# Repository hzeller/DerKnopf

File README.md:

Remote controlled volume knob
=============================

_**Knopf, der** German: button, knob (Pronounciation: /knɔpf/)_

A project to upgrade an amplifier volume knob from a simple regular
potentiometer to a digital one that still can be controlled
directly at the amplifier but also via an infrared remote control.

Replaces the regular potentiometer with a [DS1882] and a rotational encoder.
Visual feedback with a charlie-plexed LED ring.

The interesting part is the infrared remote control: another rotational encoder,
with an infrared transmitter: a wireless extension of the volume knob.

The rotational encoders have a secondary push-button function which is used to
enable muting. Another press on that button will un-mute and go back to the
original volume.

# Remote control sender
The [sender](./pcb/remote-control) is a 20mm round PCB and thus roughly the
size of the volume knob and the diameter of a CR2032 battery.

Provides a rotational encoder with an integrated button (used for 'mute'), two
Infrared LEDs to send.
Microcontroller: Attiny44. Quiescent current: < 0.2 μA. Runs on CR2032.

Top                    | Side                       | Bottom
-----------------------|----------------------------|--------------------------
||

TODO: build acryilic housing.

Code in [sender/](./sender) directory.

# DigiPot Receiver

The [receiver](pcb/digi-pot) behaves like a logarithmic stereo potentiomter.
It takes an input signal from a local rotational encoder or the infrared
signal (amplified and prepared with a Vishay TSOP75338).
It provides two 'potentiometer' outputs. The local encoder has a 32 step/turn
resolution of which 30 are used (to have a visual 'gap' between min and max
like in a regular pot).

Microcontroller: Attiny48.
Runs on +5V (digital processing) and +/-6V (Analog). For these voltge rails,
there is a little separate [power supply PCB](./pcb/power)

Code in [receiver/](./receiver) directory.

Render                      |  Bottom                      | Shallow side view
----------------------------|------------------------------|----------------------------|
| (This early revision required some bodge resistors)||

# LED Ring
The [LED ring](./pcb/led-ring) is mounted on the front-panel of the amplifier
around the volume knob. In this case, this is a 19mm knob, so the ring is 20mm.

It contains 30 charlie-plexed LEDs to display the current 'position' and the
TSOP IR module. On mute, the current volume position is blinking (controlled by
the [DigiPot](./pcb/digi-pot)).

The round board connects with the main receiver board via a 12 connect,
0.5mm pitch flat flex cable.

Render                       | Real
-----------------------------|----------------------
 | 

### Mounted on Amplifier and final Remote Control

[DS1882]: https://datasheets.maximintegrated.com/en/ds/DS1882.pdf

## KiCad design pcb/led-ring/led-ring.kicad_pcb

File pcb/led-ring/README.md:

Led-Ring
========

Led-ring with 30 charlie-plexed LEDs to display the position of the pot.
Also, since this is mounted on the front-panel, the place for the IR receiver.

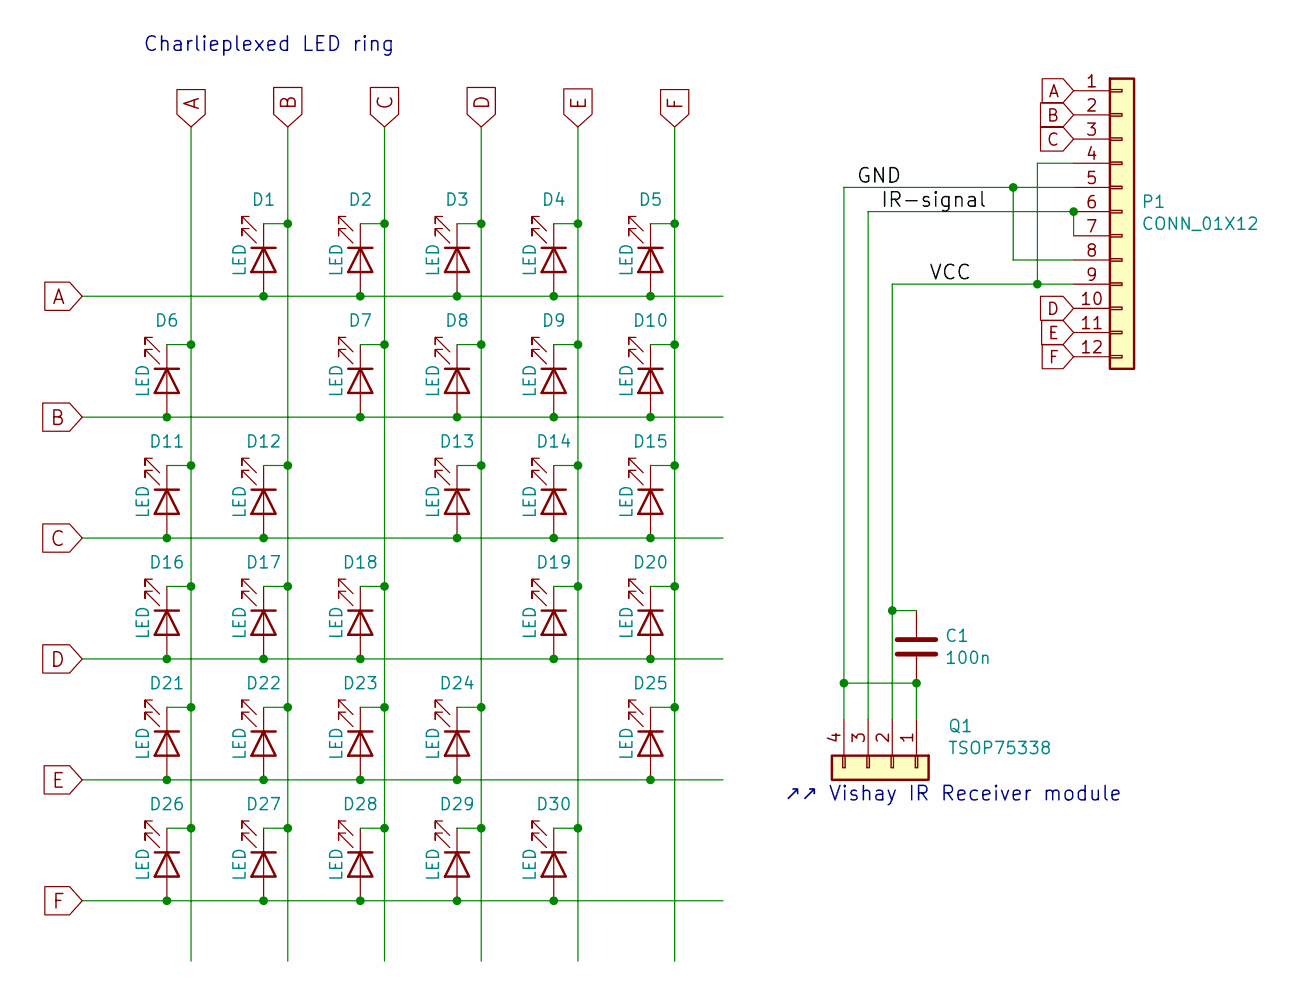
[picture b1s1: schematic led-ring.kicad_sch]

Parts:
C1: 100n; C_0603_1608Metric
D1, D2, D3, D4, D5, D6, D7, D8, D9, D10, D11, D12, D13, D14, D15, D16, D17, D18, D19, D20, D21, D22, D23, D24, D25, D26, D27, D28, D29, D30: LED; LED_0603_1608Metric
P1: CONN_01X12; FlatFlex
Q1: TSOP75338; TSOP75xx

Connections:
/GND: C1.2, P1.5, P1.8, Q1.1, Q1.4
/IR-signal: P1.6, P1.7, Q1.3
/VCC: C1.1, P1.4, P1.9, Q1.2
A: D1.2 (A), D2.2 (A), D3.2 (A), D4.2 (A), D5.2 (A), D6.1 (K), D11.1 (K), D16.1 (K), D21.1 (K), D26.1 (K), P1.1
B: D1.1 (K), D6.2 (A), D7.2 (A), D8.2 (A), D9.2 (A), D10.2 (A), D12.1 (K), D17.1 (K), D22.1 (K), D27.1 (K), P1.2
C: D2.1 (K), D7.1 (K), D11.2 (A), D12.2 (A), D13.2 (A), D14.2 (A), D15.2 (A), D18.1 (K), D23.1 (K), D28.1 (K), P1.3
D: D3.1 (K), D8.1 (K), D13.1 (K), D16.2 (A), D17.2 (A), D18.2 (A), D19.2 (A), D20.2 (A), D24.1 (K), D29.1 (K), P1.10
E: D4.1 (K), D9.1 (K), D14.1 (K), D19.1 (K), D21.2 (A), D22.2 (A), D23.2 (A), D24.2 (A), D25.2 (A), D30.1 (K), P1.11
F: D5.1 (K), D10.1 (K), D15.1 (K), D20.1 (K), D25.1 (K), D26.2 (A), D27.2 (A), D28.2 (A), D29.2 (A), D30.2 (A), P1.12

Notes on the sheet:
↗↗ Vishay IR Receiver module
Charlieplexed LED ring

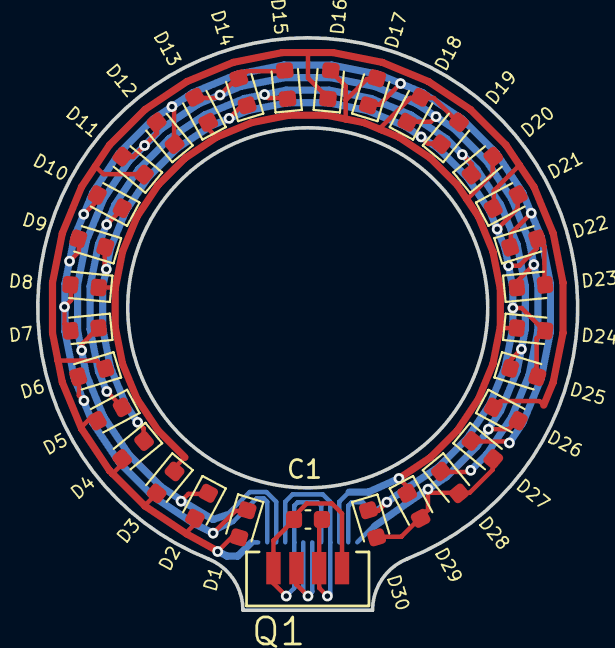
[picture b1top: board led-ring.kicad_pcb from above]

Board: 2 copper layers, 30.0 x 31.8 mm, 33 parts (1 on the bottom side), 9 nets.

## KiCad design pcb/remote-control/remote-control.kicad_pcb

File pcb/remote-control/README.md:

Remote Control
==============

The remote control, operated with an Attiny44 on a CR2032 battery. Processor
gets woken up from power down state on state change of the inputs, so quiescent
current is less than 0.2 μA.

It is not clear yet if the CR2032 increase in internal resistance over time will
be sufficient for our desired peak-current of 120mA through the IR LEDs (only
partially on, so average current ~40mA). So future revisions might consider
adding some electrolytic capacitors (but we'd need > 4700uF to power one
transmit of about 64ms * 40mA * 3V ~= 8mJ), or changing the battery (CR2450 or
even two AAA or AAAA).

With optional 1M pullups for the mechanical encoder, as these sometimes get
stuck in some half position, draining current through the pull-ups. The
standard pullups inside the attiny are aorund 60k (Note: this feature is not
used in the assembly below, just using the internal resistors.)

The programming header shown in the schematic does not have a component
associated on the board as it was too bulky.

Single-sided board for simple home-etching.

## BOM
  * 1x rotational encoder with push-button (here: EN11-HSB1AQ20, but might consider EN11-HSM1AF15 in the future for better mounting. See [EN11-datasheet])
  * 1x Attiny44
  * 1x 22μF ceramic capacitor (1206)
  * 1x 100n ceramic capacitor (0603)
  * 2x 1M resistor (0603)
  * 1x 4.7Ohm resistor (0805)
  * 1x MTM232270 N-channel Mosfet (SOT-323)

Top                    | Side                       | Bottom
-----------------------|----------------------------|--------------------------
||

[EN11-datasheet]: http://www.bitechnologies.com/pdfs/en11.pdf

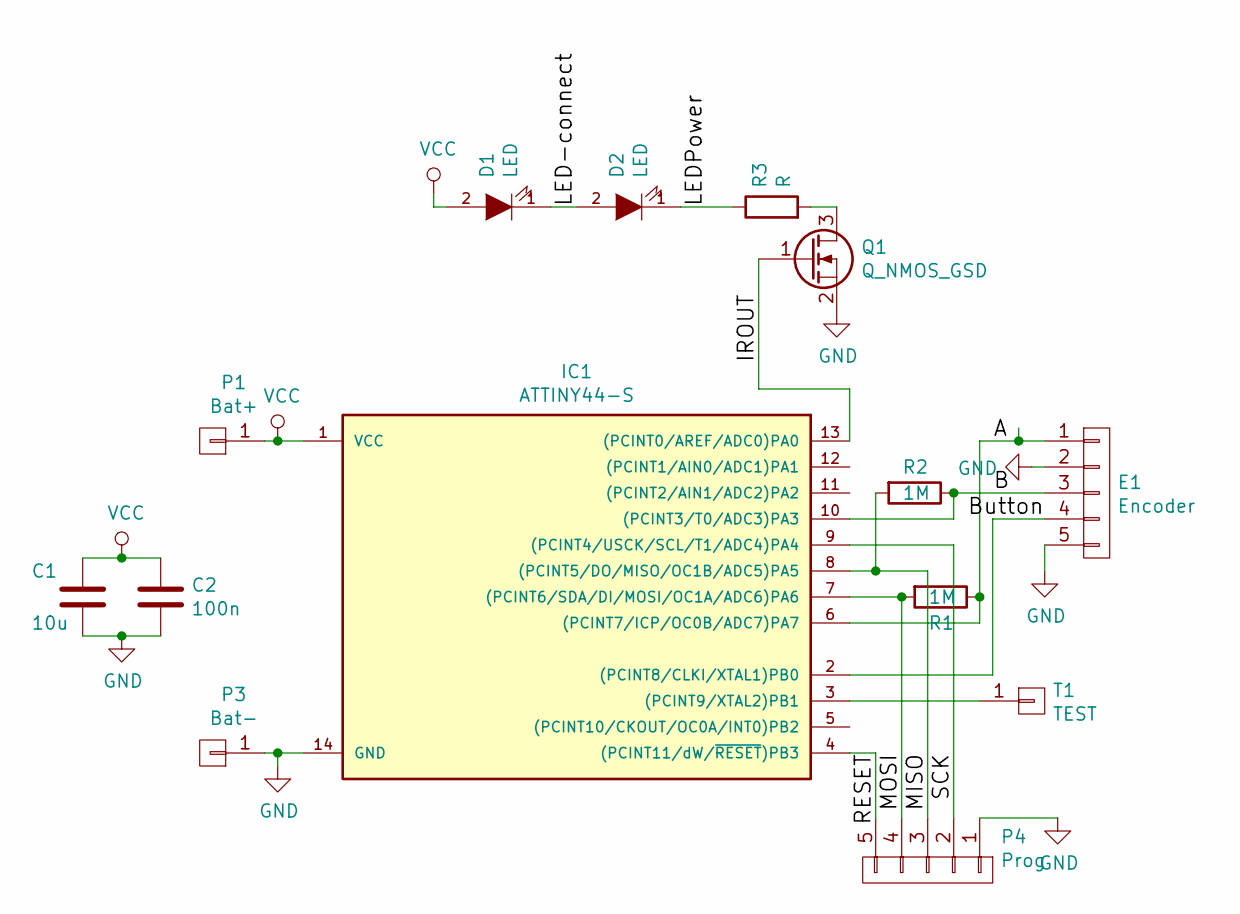
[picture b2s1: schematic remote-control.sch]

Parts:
C1: 10u; C_0805
C2: 100n
D1, D2: LED; LED-5MM
E1: Encoder; MechanicalEncoder
IC1: ATTINY44-S; SOIC-14_N
P1: Bat+; Pin_Header_Straight_1x01
P3: Bat-; Pin_Header_Straight_1x01
P4: Prog
Q1: Q_NMOS_GSD; SOT-323
R1, R2: 1M; R_0603
R3: R; R_0805
T1: TEST; TestPoint

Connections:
/A: E1.1, IC1.6 ((PCINT7/ICP/OC0B/ADC7)PA7), R1.1
/B: E1.3, IC1.10 ((PCINT3/T0/ADC3)PA3), R2.1
/Button: E1.4, IC1.2 ((PCINT8/CLKI/XTAL1)PB0)
/IROUT: IC1.13 ((PCINT0/AREF/ADC0)PA0), Q1.1 (G)
/LED-connect: D1.1 (K), D2.2 (A)
/LEDPower: D2.1 (K), R3.1
/MISO: IC1.8 ((PCINT5/DO/MISO/OC1B/ADC5)PA5), P4.3, R2.2
/MOSI: IC1.7 ((PCINT6/SDA/DI/MOSI/OC1A/ADC6)PA6), P4.4, R1.2
/RESET: IC1.4 ((PCINT11/dW/~RESET~)PB3), P4.5
/SCK: IC1.9 ((PCINT4/USCK/SCL/T1/ADC4)PA4), P4.2
GND: C1.2, C2.2, E1.2, E1.5, IC1.14 (GND), P3.1, P4.1, Q1.2 (S)
unnamed: IC1.3 ((PCINT9/XTAL2)PB1), T1.1
unnamed: Q1.3 (D), R3.2
VCC: C1.1, C2.1, D1.2 (A), IC1.1 (VCC), P1.1

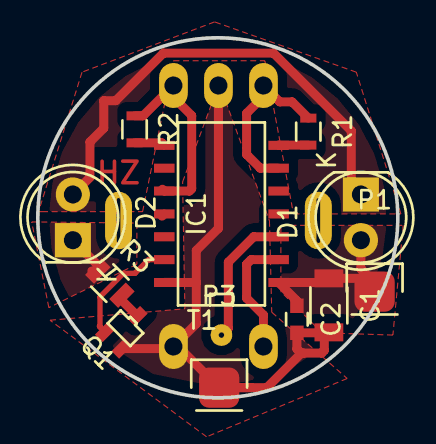
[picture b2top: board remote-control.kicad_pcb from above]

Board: 2 copper layers, 20.0 x 20.0 mm, 13 parts (1 on the bottom side), 12 nets.

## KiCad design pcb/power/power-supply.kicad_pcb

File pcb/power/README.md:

Power supply
============

The DigiPot needs 5V for digital operation and +/- 6V for the analog part.
Assuming that we already have some symmetric power in the amplifier, this
creates the necessary voltages. The current demands on the analog rails are
miniscule, so small SOT89-3 are sufficient for the task.

The 5V rail needs something in the 30mA range (operate microcontroller,
LEDs on LED ring and optical encoder), so depending on the input
voltage that could be some noticeable generated heat, hence we use a TO220 case.

Single sided board for simple home-etching.

## BOM

 * 1x 78L06 SOT89-3
 * 1x 79L06 SOT89-3
 * 1x 7805 TO220
 * 3x 100n capacitor, 0805
 * 2x 10uF ceramic capacitor, 50V, 1206

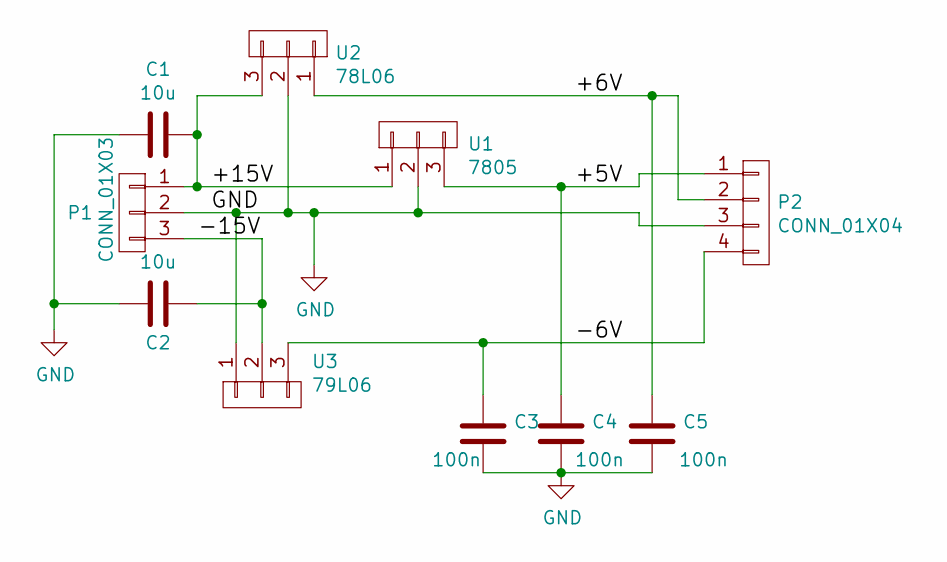
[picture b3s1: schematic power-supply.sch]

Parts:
C1, C2: 10u; C_1206_HandSoldering
C3, C4, C5: 100n; C_0805_HandSoldering
P1: CONN_01X03; Pin_Header_Straight_1x03
P2: CONN_01X04; Pin_Header_Straight_1x04
U1: 7805; TO-220_Neutral123_Horizontal_LargePads
U2: 78L06; SOT89-3_Housing_Handsoldering
U3: 79L06; SOT89-3_Housing_Handsoldering

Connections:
/+5V: C4.1, P2.1, U1.3
/+6V: C5.1, P2.2, U2.1
/+15V: C1.1, P1.1, U1.1, U2.3
/-6V: C3.1, P2.4, U3.3
/-15V: C2.1, P1.3, U3.2
GND: C1.2, C2.2, C3.2, C4.2, C5.2, P1.2, P2.3, U1.2, U2.2, U3.1

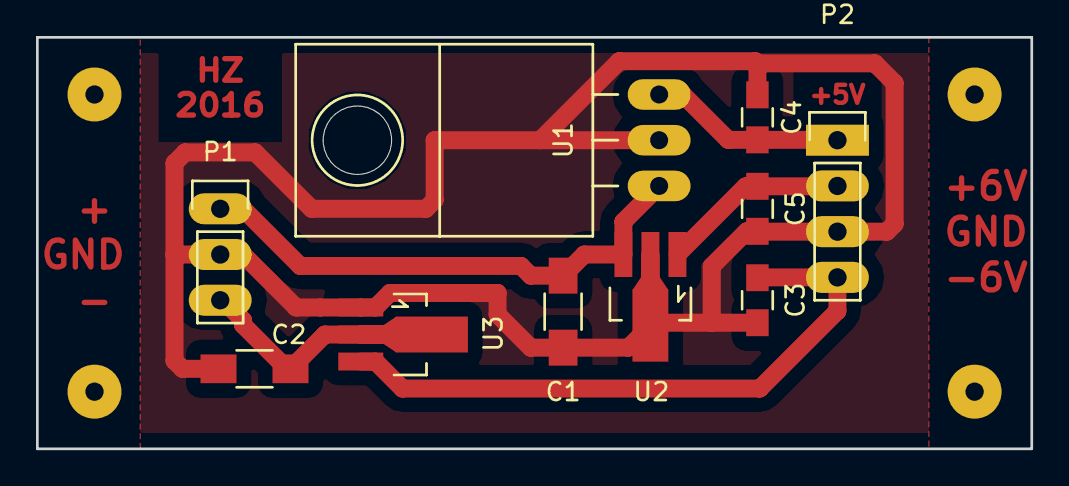
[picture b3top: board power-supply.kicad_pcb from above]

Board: 2 copper layers, 55.2 x 22.9 mm, 14 parts (0 on the bottom side), 6 nets.

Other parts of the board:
R: D; Pin_Header_Straight_1x01
R#2, R#3, R#4: D; Pin_Header_Straight_1x01

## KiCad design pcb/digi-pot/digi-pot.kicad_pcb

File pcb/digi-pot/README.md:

DigiPot
=======

The actual simulated pot with connectors for the LED ring, the IR receiver and
a local optical rotational encoder to have the feel of a local potentiometer.

This encoder replaces an existing high-quality ALPS potentiometer with 30 detents.
It is surprisingly hard to find a mechanical encoder with the same solid feel
and 32 detents (most mechanical enoders only go to 20 steps/turn).

The CUI optical encoder is perfect for this job but about as expensive as the
potentiometer it replaces.

## BOM

 * 2x 4.7k 0603 resistor
 * 4x 100n 0603 capacitor
 * 2x (4x75 Ohm) resistor network.
 * 1x Attiny48
 * 1x DS1882
 * 1x CUI C14D32P-A3 optical encoder.
 * 1x FlatFlex 12Pin connector.

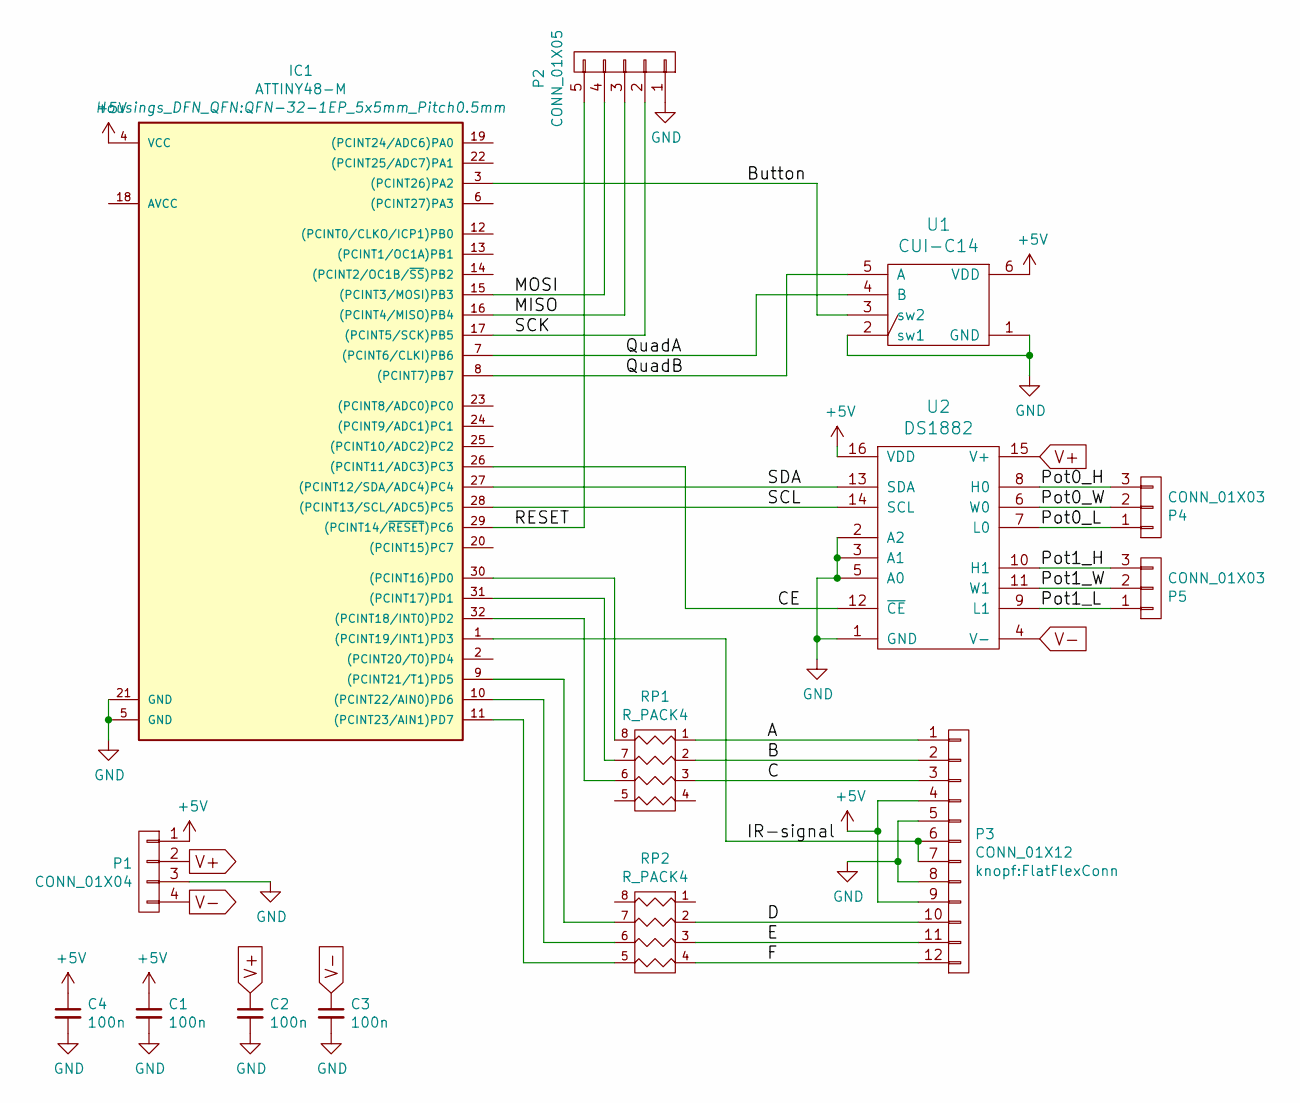
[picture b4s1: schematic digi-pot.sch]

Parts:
C1, C2, C3, C4: 100n; C_0805
IC1: ATTINY48-M; QFN-32-1EP_5x5mm_Pitch0.5mm
P1: CONN_01X04; Pin_Header_Straight_1x04
P2: CONN_01X05; Pin_Header_Straight_1x05
P3: CONN_01X12; FlatFlexConn
P4, P5: CONN_01X03; Pin_Header_Straight_1x03
RP1, RP2: R_PACK4; R_Array_Convex_4x0603
U1: CUI-C14
U2: DS1882; TSSOP-16_4.4x5mm_Pitch0.65mm

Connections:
+5V: C1.1, C4.1, IC1.4 (VCC), P1.1, P3.4, P3.9, U1.6 (VDD), U2.16 (VDD); also elsewhere on the board
/A: P3.1, RP1.1
/B: P3.2, RP1.2
/Button: IC1.3 ((PCINT26)PA2), U1.3 (sw2)
/C: P3.3, RP1.3
/CE: IC1.26 ((PCINT11/ADC3)PC3), U2.12 (~CE)
/D: P3.10, RP2.2
/E: P3.11, RP2.3
/F: P3.12, RP2.4
/IR-signal: IC1.1 ((PCINT19/INT1)PD3), P3.6, P3.7
/MISO: IC1.16 ((PCINT4/MISO)PB4), P2.3
/MOSI: IC1.15 ((PCINT3/MOSI)PB3), P2.4
/Pot0_H: P4.3, U2.8 (H0)
/Pot0_L: P4.1, U2.7 (L0)
/Pot0_W: P4.2, U2.6 (W0)
/Pot1_H: P5.3, U2.10 (H1)
/Pot1_L: P5.1, U2.9 (L1)
/Pot1_W: P5.2, U2.11 (W1)
/QuadA: IC1.7 ((PCINT6/CLKI)PB6), U1.4 (B)
/QuadB: IC1.8 ((PCINT7)PB7), U1.5 (A)
/RESET: IC1.29 ((PCINT14/~RESET~)PC6), P2.5
/SCK: IC1.17 ((PCINT5/SCK)PB5), P2.2
/SCL: IC1.28 ((PCINT13/SCL/ADC5)PC5), U2.14 (SCL); also elsewhere on the board
/SDA: IC1.27 ((PCINT12/SDA/ADC4)PC4), U2.13 (SDA); also elsewhere on the board
GND: C1.2, C2.2, C3.2, C4.2, IC1.5 (GND), IC1.21 (GND), P1.3, P2.1, P3.5, P3.8, U1.1 (GND), U1.2 (sw1), U2.1 (GND), U2.2 (A2), U2.3 (A1), U2.5 (A0)
unnamed: IC1.9 ((PCINT21/T1)PD5), RP2.7 (R2)
unnamed: IC1.10 ((PCINT22/AIN0)PD6), RP2.6 (R3)
unnamed: IC1.11 ((PCINT23/AIN1)PD7), RP2.5 (R4)
unnamed: IC1.30 ((PCINT16)PD0), RP1.8 (R1)
unnamed: IC1.31 ((PCINT17)PD1), RP1.7 (R2)
unnamed: IC1.32 ((PCINT18/INT0)PD2), RP1.6 (R3)
V+: C2.1, P1.2, U2.15 (V+)
V-: C3.1, P1.4, U2.4 (V-)

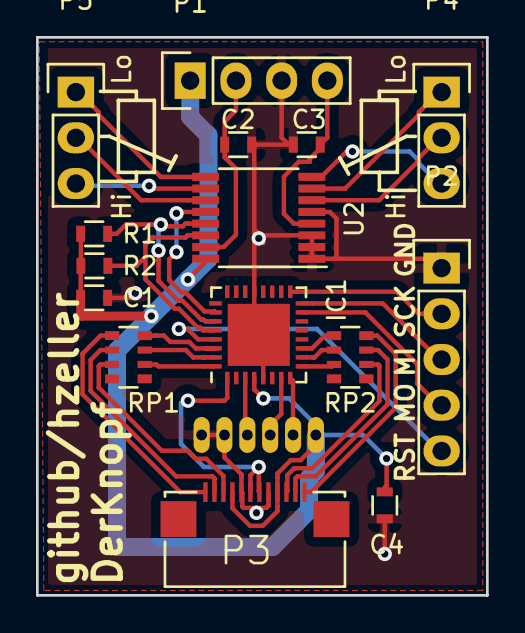
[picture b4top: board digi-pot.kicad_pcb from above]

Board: 2 copper layers, 25.0 x 31.0 mm, 16 parts (1 on the bottom side), 33 nets.

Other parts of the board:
R1, R2: 4k7; R_0603

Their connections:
+5V: R1.1, R2.1; also elsewhere on the board
/SCL: R2.2; also elsewhere on the board
/SDA: R1.2; also elsewhere on the board

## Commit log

2015-03-08 o First version of transmitter. Based on ATMEGA8.
2015-03-08 o Simple receiver. At this point, just dumping what it received to the serial line.
2015-03-08 o Make things a bit easier to read: c-basic-offset 4
2015-03-08 o Make ready for 4Mhz operation.
2015-03-09 o Fix race-condition as bottom-half operation might not be called timely (in particular a 4MHz).
2015-03-09 o First wave more closely to chosen frequency.
2015-03-09 o Simplify literals specifying what to send.
2015-03-09 o Rotate stepper on reciept of "more" or "less"
2015-03-09 o Add readme.
2015-03-09 o Update README.
2015-03-10 o Add forgotten files.
2015-03-11 o keep in 80 characters; smallish cleanup.
2015-03-13 o doh, the rotary encoder that will be used has only 12 detents.
2015-03-14 o Add bottom cut.
2015-03-14 o Move case to sub-dir
2015-03-14 o Mounting of the bottom to the case. o better modelling of LEDs. o Don't recess mounting hole for top of case for flat printing surface.
2015-03-14 o testing with more prominent knurls o Battery blades accessible for mounting. o battery text visible from below.
2015-03-14 o Make text not quite as embossed.
2015-03-15 o Move to attiny24 and make basic sleep work.
2015-03-15 o Smaller interrupt handler for waking up.
2015-03-19 o Better naming of input port.
2015-03-19 o case tweaks.
2016-10-08 o Use appropriate int type for the platform (int8_t instead of int)
2016-10-08 o moar warnings.
2016-10-08 o Start LED-ring PCB
2016-10-09 o Add flat-flex footprint.
2016-10-09 o seed net-starts.
2016-10-09 o Get polygons started. Wired up first couple of LEDs.
2016-10-09 o Wire up LEDs.
2016-10-09 o make circle traces thicker.
2016-10-09 o Move outer rings to top layer to avoid a couple of vias.
2016-10-09 o Remove tail-traces - traces after the last via that uses them.
2016-10-09 o Fix accidentally set aux origin - that makes oshpark unhappy.
2016-10-09 o Add IR receiver. o Shape ring in a way so that receiver fits.
2016-10-09 o Make sure to only include the git version of the PCB.
2016-10-23 o add project library.
2016-10-23 o Add cui lib.
2016-10-23 o add CUI footprint.
2016-10-23 o move knopf.pretty one level up.
2016-10-23 o use knopf.pretty one level up.
2016-10-23 o add base for digi pot
2016-10-23 o first schematic
2016-10-24 o complete schematic
2016-10-24 o First version PCB
2016-10-24 o Make sure gitversion string fits on board.
2016-10-24 o Better marking of input voltages.
2016-11-01 o Add little power supply breakout; one-sided for simple hand-etching.
2016-11-01 o Add marking.
2016-11-06 o read local quadrature encoder. o output current pos to charlie-plexed LED ring. o Remove motor output.
2016-11-07 o First hookup of the DS1882
2016-11-07 o Add pull-ups for I2C bus. o smallish changes in power supply.
2016-11-07 o store last state in eeprom. o discard early reads of encoder to not create a false reading right after reset.
2016-11-12 o first version remote control.
2016-11-12 o Make IR engergy storage 1206 SMD size o add 0603 package for 100n bypass.
2016-11-15 o Make transmitter work with new PCB.
2016-11-15 o Receive button press and connect to mute.
2016-11-15 o add histogram for determining best cut-off between 0 and 1 bit.
2016-11-15 o Make it possible to work without serial.
2016-11-18 o interrupt actually did work, just wrong lines selected.
2016-11-19 o update Readme with the new direction of project (previously: controlling stepper motor, now DS1882).
2016-11-19 o Change from development set-up (Atmega8) to production set-up (Attiny48): no UART serial connection anymore. different IO-pins.
2016-11-19 o Add serial communication code for set-ups that have UART
2016-11-19 o add forgotten footprint: FlatFlex connector
2016-11-19 o connect flat flex connector ground to ground.
2016-11-19 o Initialize fuses for Attiny48 o Honor different pinout of LEDs in PCB. o Don't initialize histogram if we're not using it.
2016-11-20 o move TSOP75 into right directory.
2016-11-20 o Update README with some rudimentary pictures.
2016-11-20 o light up led-ring picture.
2016-11-20 o Flipped A/B in production board.
2016-11-20 o Update receiver image.
2016-11-20 o simplify initialization of quad decoder. o Initialization: wait until rotational encoder has settled.
2016-11-20 o Remove a couple of non-useful 3D component renderings
2016-11-20 o Add some 3D renderings.
2016-11-20 o Add some basic READMEs for the PCB directories.
2016-11-20 o add a couple more cross-links between readmes
2016-11-20 o Add BOM for remote control sender. o Add battery considerations and possible future revision changes.
2016-11-21 o Update remote control: ready for a larger battery and housing o start housing.
2016-11-21 o larger screw holes.
2016-11-21 o smaller set.
2016-11-21 o large hole
2016-11-30 o Individualized level steps to dB mapping (now allows lowest level). o Remove unused secondary remote control.
2016-12-01 o Add amplifier image.
2017-02-04 o re-arrange files a bit so that they look better in gerbv.
2017-02-05 o Placing paste close to the copper is more logical.
2017-05-02 o Add image.
2024-02-14 led-ring: Update to Kicad 7
    * Use new schematic symbols and footprints
    * adjust board configuration for good solder stop expansion
    * Update Python script to work with current kicad.
2024-02-14 Add shell.nix for easy set-up of environment
2024-02-14 Update gitignore to match current filenames.
2024-02-14 Rotate LED designators to read horizontally.
2024-02-14 Move designators out of view.
    The LED numbering is not really helping while populating, but
    clutters the look of the ring that we want to keep focused on the
    LEDs.
